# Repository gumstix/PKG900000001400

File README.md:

# Gumstix Raspberry Pi CM4 Development Board
## PKG900000001400 ![PKG900000001400][thumbnail]

Designed by Gumstix in Geppetto, the **Gumstix Raspberry Pi CM4 Development Board** brings the best of the CM4 to light, from PCIe to Gigabit Ethernet to dual CSI2 cameras.  Whether you're building a NAS server or a face-detecting robot, The CM4 Development board has built-in features that will help your project along.  It provides the following connections for breaking out the features of the Raspberry Pi CM4:

* Raspberry Pi 4 Header
* USB-UART Console Port
* DSI connector for connecting to displays
* 2 x CSI2 connector for connecting a camera
* HDMI port for audio/display
* Gigabit Ethernet port
* USB Type-A port for expandability
* M.2 (M Key) with single lane PCIe, compatible with 2280 NVMe drives and Google Coral

The CM4 Development board is ideal for various applications, Including:
* Network attached mass storage (NAS)
* Media Centers
* Edge AI
* Smart home management

__Links:__
* [AutoDoc Datasheet][autodoc]
* [Specifications][spec]
* [Store Page][store]
* [Schematics and Layout][hardware]

[thumbnail]: https://d3iwea566ns1n1.cloudfront.net/images/product/1ae94bd9fed173c4b6867992084763ec15bd388f.png
[autodoc]: PKG900000001400_AutoDoc.pdf
[spec]: PKG900000001400_SpecSheet.pdf
[store]: https://store.gumstix.com/cm4-development-board/
[hardware]: hardware/hardware.md
[firmware]: firmware/firmware.md

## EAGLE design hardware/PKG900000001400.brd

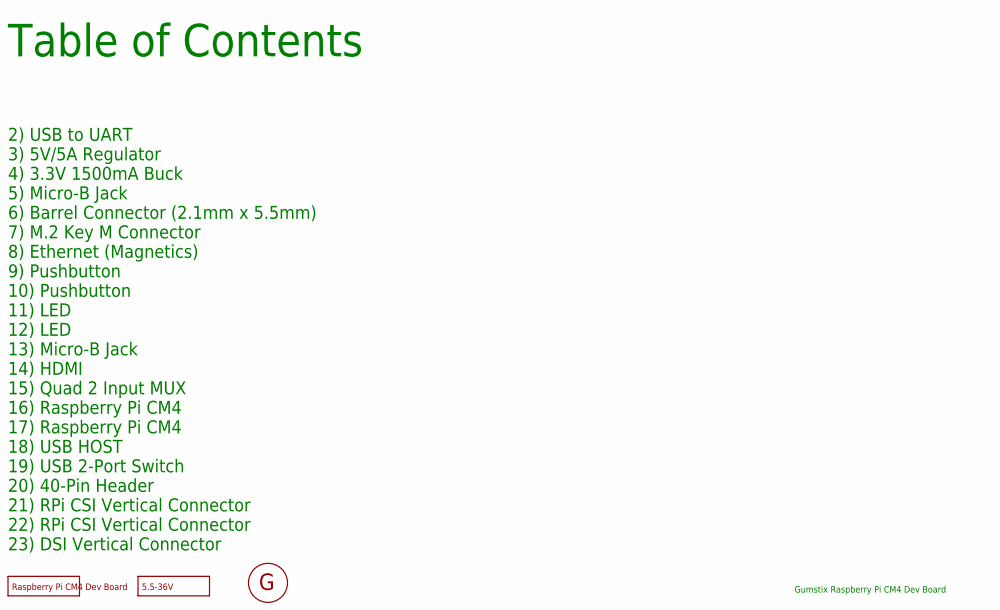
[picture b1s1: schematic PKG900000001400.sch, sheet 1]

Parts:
FD1, FD2, FD3, FD4, FD5, FD6, FD7, FD8: DNP; FIDUCIAL
U$3: DNP; GEPPETTO_LABEL
U$4: DNP; GEPPETTO_LOGO_SILK10
U$6: DNP; TIP_POSITIVE_LABEL; VOLTAGE 5.5-36V

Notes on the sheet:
Table of Contents
Gumstix Raspberry Pi CM4 Dev Board
2) USB to UART
3) 5V/5A Regulator
4) 3.3V 1500mA Buck
5) Micro-B Jack
6) Barrel Connector (2.1mm x 5.5mm)
7) M.2 Key M Connector
8) Ethernet (Magnetics)
9) Pushbutton
10) Pushbutton
11) LED
12) LED
13) Micro-B Jack
14) HDMI
15) Quad 2 Input MUX
16) Raspberry Pi CM4
17) Raspberry Pi CM4
18) USB HOST
19) USB 2-Port Switch
20) 40-Pin Header
21) RPi CSI Vertical Connector
22) RPi CSI Vertical Connector
23) DSI Vertical Connector

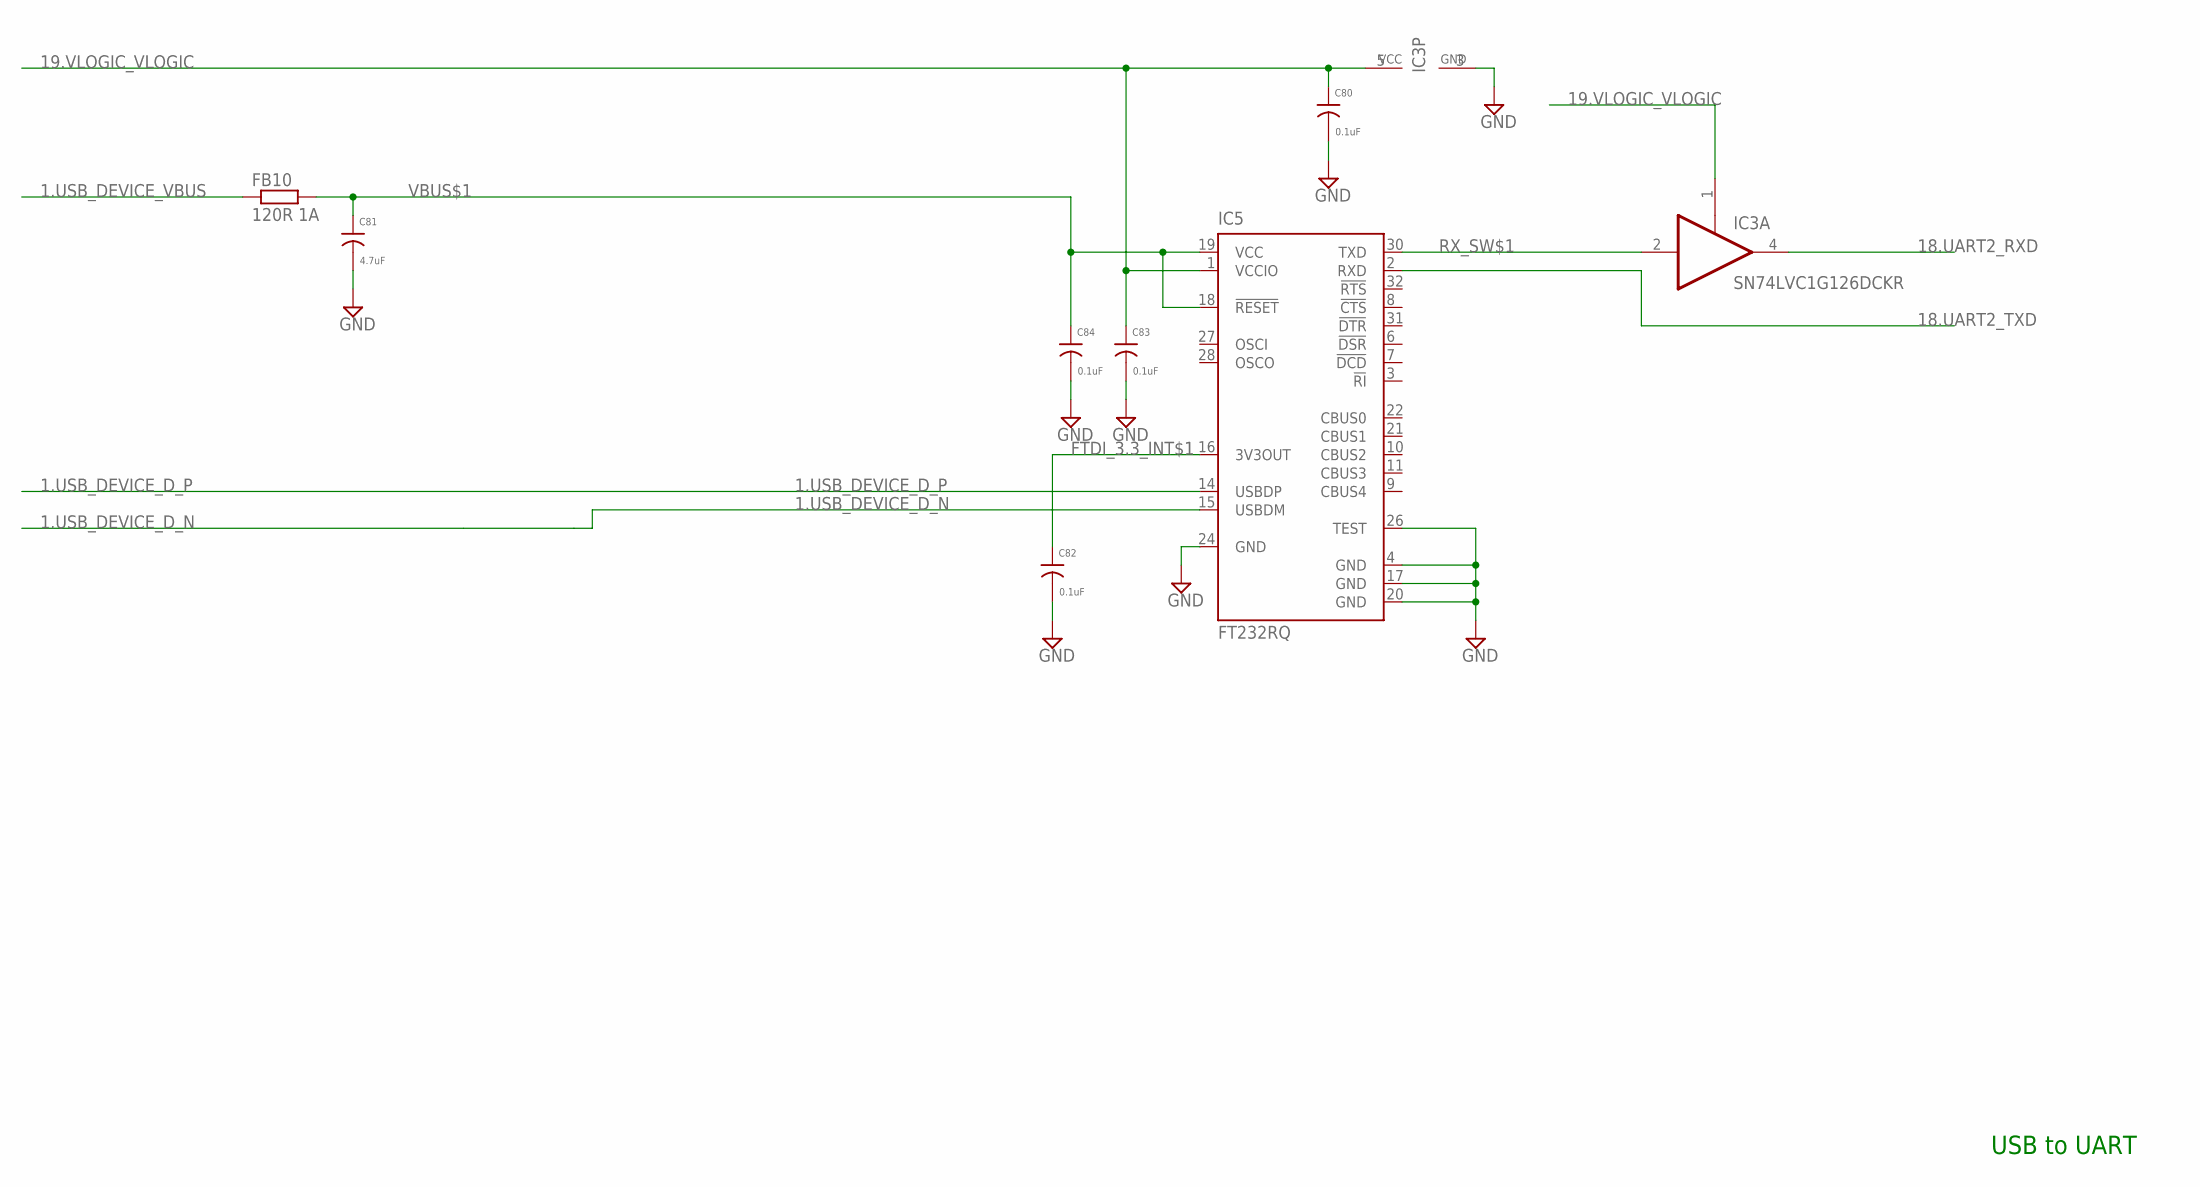
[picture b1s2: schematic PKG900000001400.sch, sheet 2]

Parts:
C80, C82, C83, C84: 0.1uF; 0201
C81: 4.7uF; 0603
FB10: 120R 1A; 0402
IC3: SN74LVC1G126DCKR; SC70-5
IC5: FT232RQ; QFN32

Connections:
1.USB_DEVICE_D_N: IC5.15 (USBDM); also elsewhere on the board
1.USB_DEVICE_D_P: IC5.14 (USBDP); also elsewhere on the board
1.USB_DEVICE_VBUS: FB10.1; also elsewhere on the board
18.UART2_RXD: IC3.4 (O); also elsewhere on the board
18.UART2_TXD: IC5.2 (RXD); also elsewhere on the board
19.VLOGIC_VLOGIC: C80.1, C83.1, IC3.1 (OE), IC3.5 (VCC), IC5.1 (VCCIO); also elsewhere on the board
FTDI_3.3_INT$1: C82.1, IC5.16 (3V3OUT)
GND: C80.2, C81.2, C82.2, C83.2, C84.2, IC3.3 (GND), IC5.4 (GND), IC5.17 (GND), IC5.20 (GND), IC5.24 (GND), IC5.26 (TEST); also elsewhere on the board
RX_SW$1: IC3.2 (I), IC5.30 (TXD)
VBUS$1: C81.1, C84.1, FB10.2, IC5.18 (!RESET), IC5.19 (VCC)

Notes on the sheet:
USB to UART

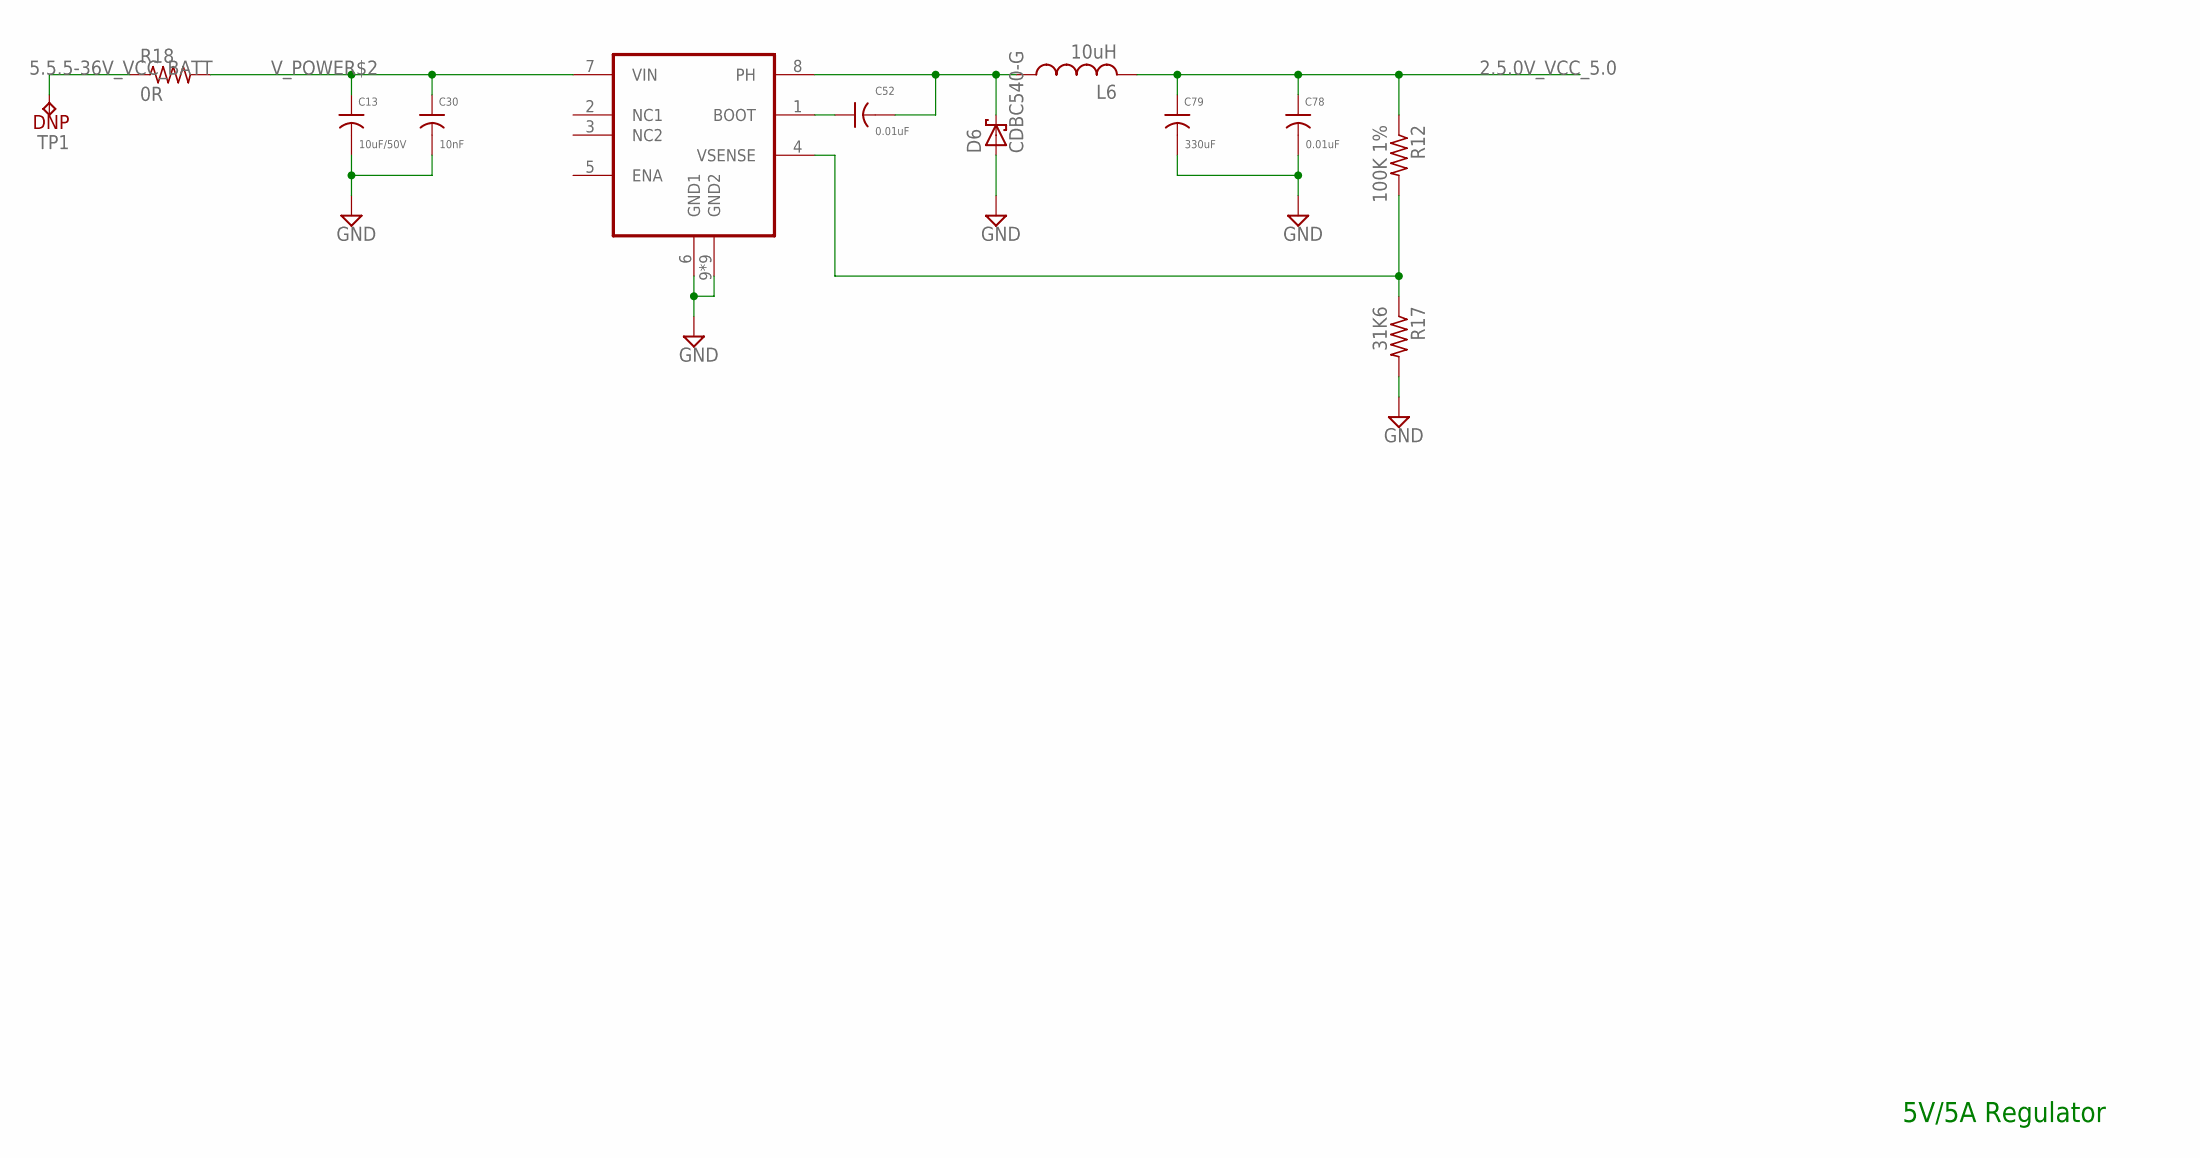
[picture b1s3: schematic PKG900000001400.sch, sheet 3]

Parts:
C13: 10uF/50V; 1206
C30: 10nF; 0603
C52, C78: 0.01uF; 0201
C79: 330uF; PANASONIC_F
D6: CDBC540-G; DO-214AB
L6: 10uH; 3232DZ
R12: 100K 1%; 0201
R17: 31K6; 0402
R18: 0R; 0805
TP1: DNP; TP0500
U7: TPS5450; 8SO_POWERPAD

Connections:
2.5.0V_VCC_5.0: C78.1, C79.+ (1), L6.2, R12.1; also elsewhere on the board
5.5.5-36V_VCC_BATT: R18.1, TP1.1; also elsewhere on the board
BOOT$2: C52.1, U7.1 (BOOT)
GND: C13.2, C30.2, C78.2, C79.- (2), D6.A, R17.2, U7.6 (GND1), U7.9 (GND2), U7.PWRPAD1 (GND2), U7.PWRPAD2 (GND2), U7.PWRPAD3 (GND2), U7.PWRPAD4 (GND2), U7.PWRPAD5 (GND2), U7.PWRPAD6 (GND2), U7.PWRPAD7 (GND2), U7.PWRPAD8 (GND2); also elsewhere on the board
PH$2: C52.2, D6.C, L6.1, U7.8 (PH)
VSENSE$2: R12.2, R17.1, U7.4 (VSENSE)
V_POWER$2: C13.1, C30.1, R18.2, U7.7 (VIN)

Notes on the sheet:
5V/5A Regulator

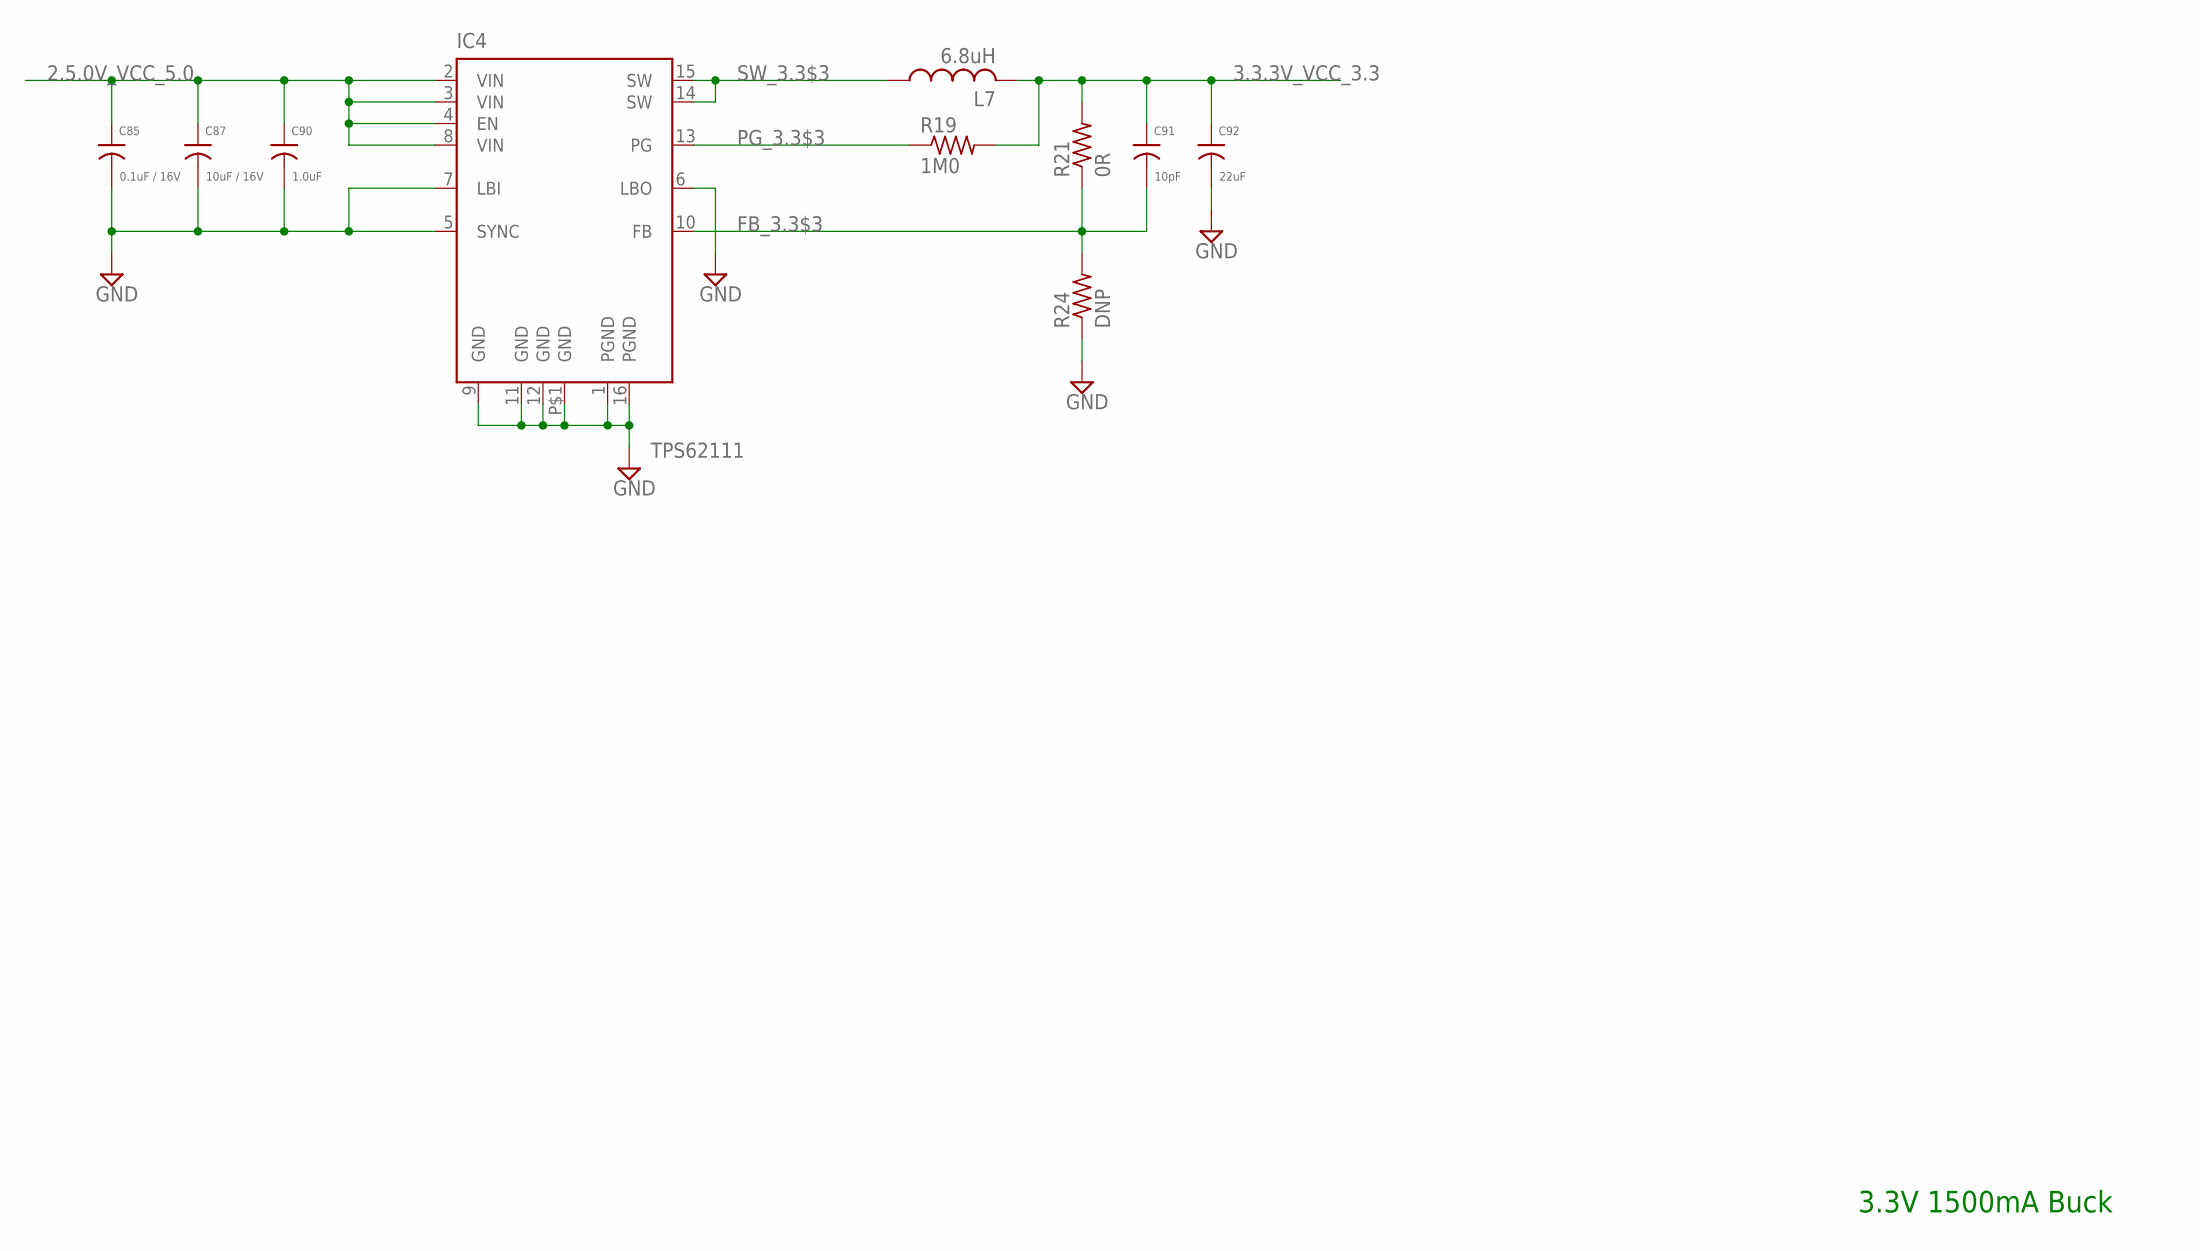
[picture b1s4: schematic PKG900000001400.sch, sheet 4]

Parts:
C85: 0.1uF / 16V; 0402
C87: 10uF / 16V; 0805
C90: 1.0uF; 0402
C91: 10pF; 0201
C92: 22uF; 0805
IC4: TPS62111; PQFP16
L7: 6.8uH; 1515
R19: 1M0; 0201
R21: 0R; 0402
R24: DNP; 0402

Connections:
2.5.0V_VCC_5.0: C85.1, C87.1, C90.1, IC4.2 (VIN), IC4.3 (VIN), IC4.4 (EN), IC4.8 (VIN); also elsewhere on the board
3.3.3V_VCC_3.3: C91.1, C92.1, L7.2, R19.2, R21.2; also elsewhere on the board
FB_3.3$3: C91.2, IC4.10 (FB), R21.1, R24.2
GND: C85.2, C87.2, C90.2, C92.2, IC4.1 (PGND), IC4.5 (SYNC), IC4.6 (LBO), IC4.7 (LBI), IC4.9 (GND), IC4.11 (GND), IC4.12 (GND), IC4.16 (PGND), IC4.P$1 (GND), R24.1; also elsewhere on the board
PG_3.3$3: IC4.13 (PG), R19.1
SW_3.3$3: IC4.14 (SW), IC4.15 (SW), L7.1

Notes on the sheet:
3.3V 1500mA Buck

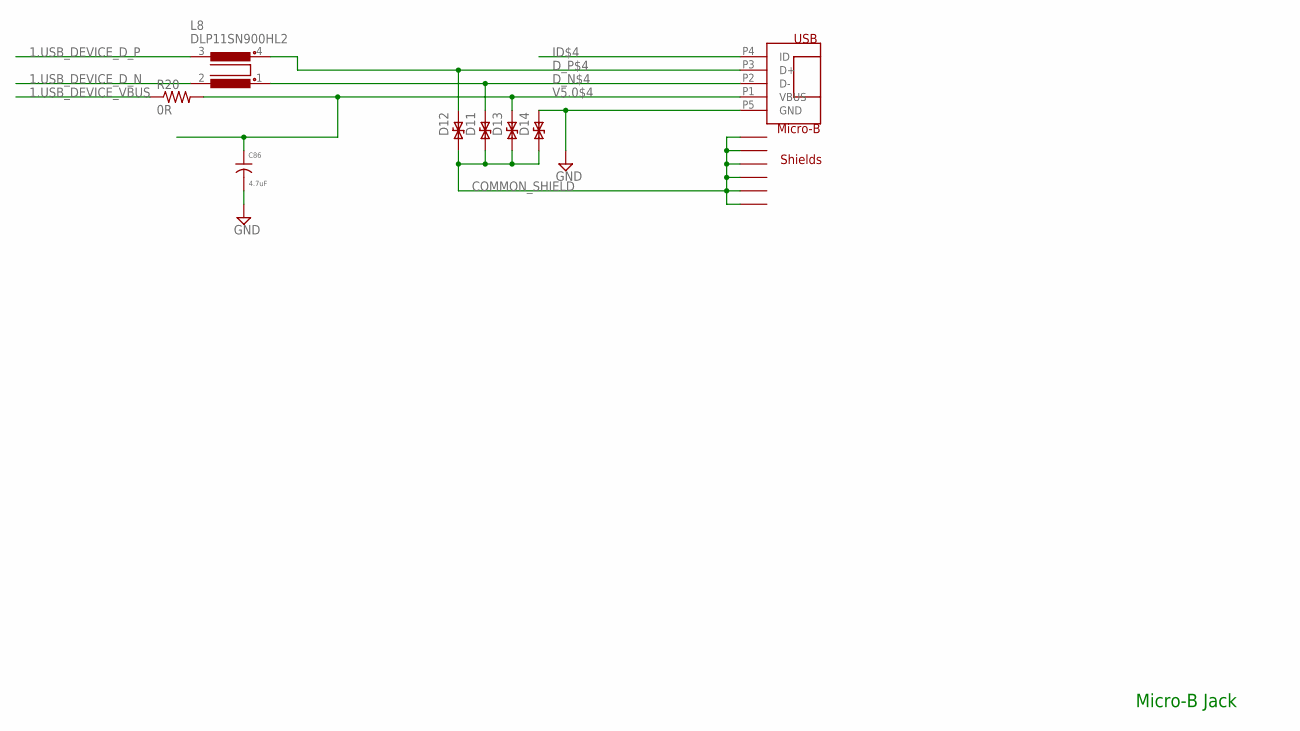
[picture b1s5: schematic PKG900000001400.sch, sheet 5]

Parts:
C86: 4.7uF; 0603
D11, D12: PS04LTVA1; D0402
D13, D14: B72590D50A060; D0402
J6: USB_MICRO_B
L8: DLP11SN900HL2; 0504-DLP11S
R20: 0R; 0201

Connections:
1.USB_DEVICE_D_N: L8.2; also elsewhere on the board
1.USB_DEVICE_D_P: L8.3; also elsewhere on the board
1.USB_DEVICE_VBUS: R20.1; also elsewhere on the board
COMMON_SHIELD: D11.P1, D12.P1, D13.P1, D14.P1, J6.COMMON_SHEILD1 (COMMON_SHIELD1), J6.COMMON_SHEILD2 (COMMON_SHIELD2), J6.COMMON_SHEILD3 (COMMON_SHIELD3), J6.COMMON_SHEILD4 (COMMON_SHIELD4), J6.COMMON_SHEILD5 (COMMON_SHIELD5), J6.COMMON_SHEILD6 (COMMON_SHIELD6); also elsewhere on the board
D_N$4: D11.P2, J6.P2 (D-), L8.1
D_P$4: D12.P2, J6.P3 (D+), L8.4
GND: C86.2, D14.P2, J6.P5 (GND); also elsewhere on the board
ID$4: J6.P4 (ID)
V5.0$4: C86.1, D13.P2, J6.P1 (VBUS), R20.2

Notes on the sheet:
Micro-B Jack

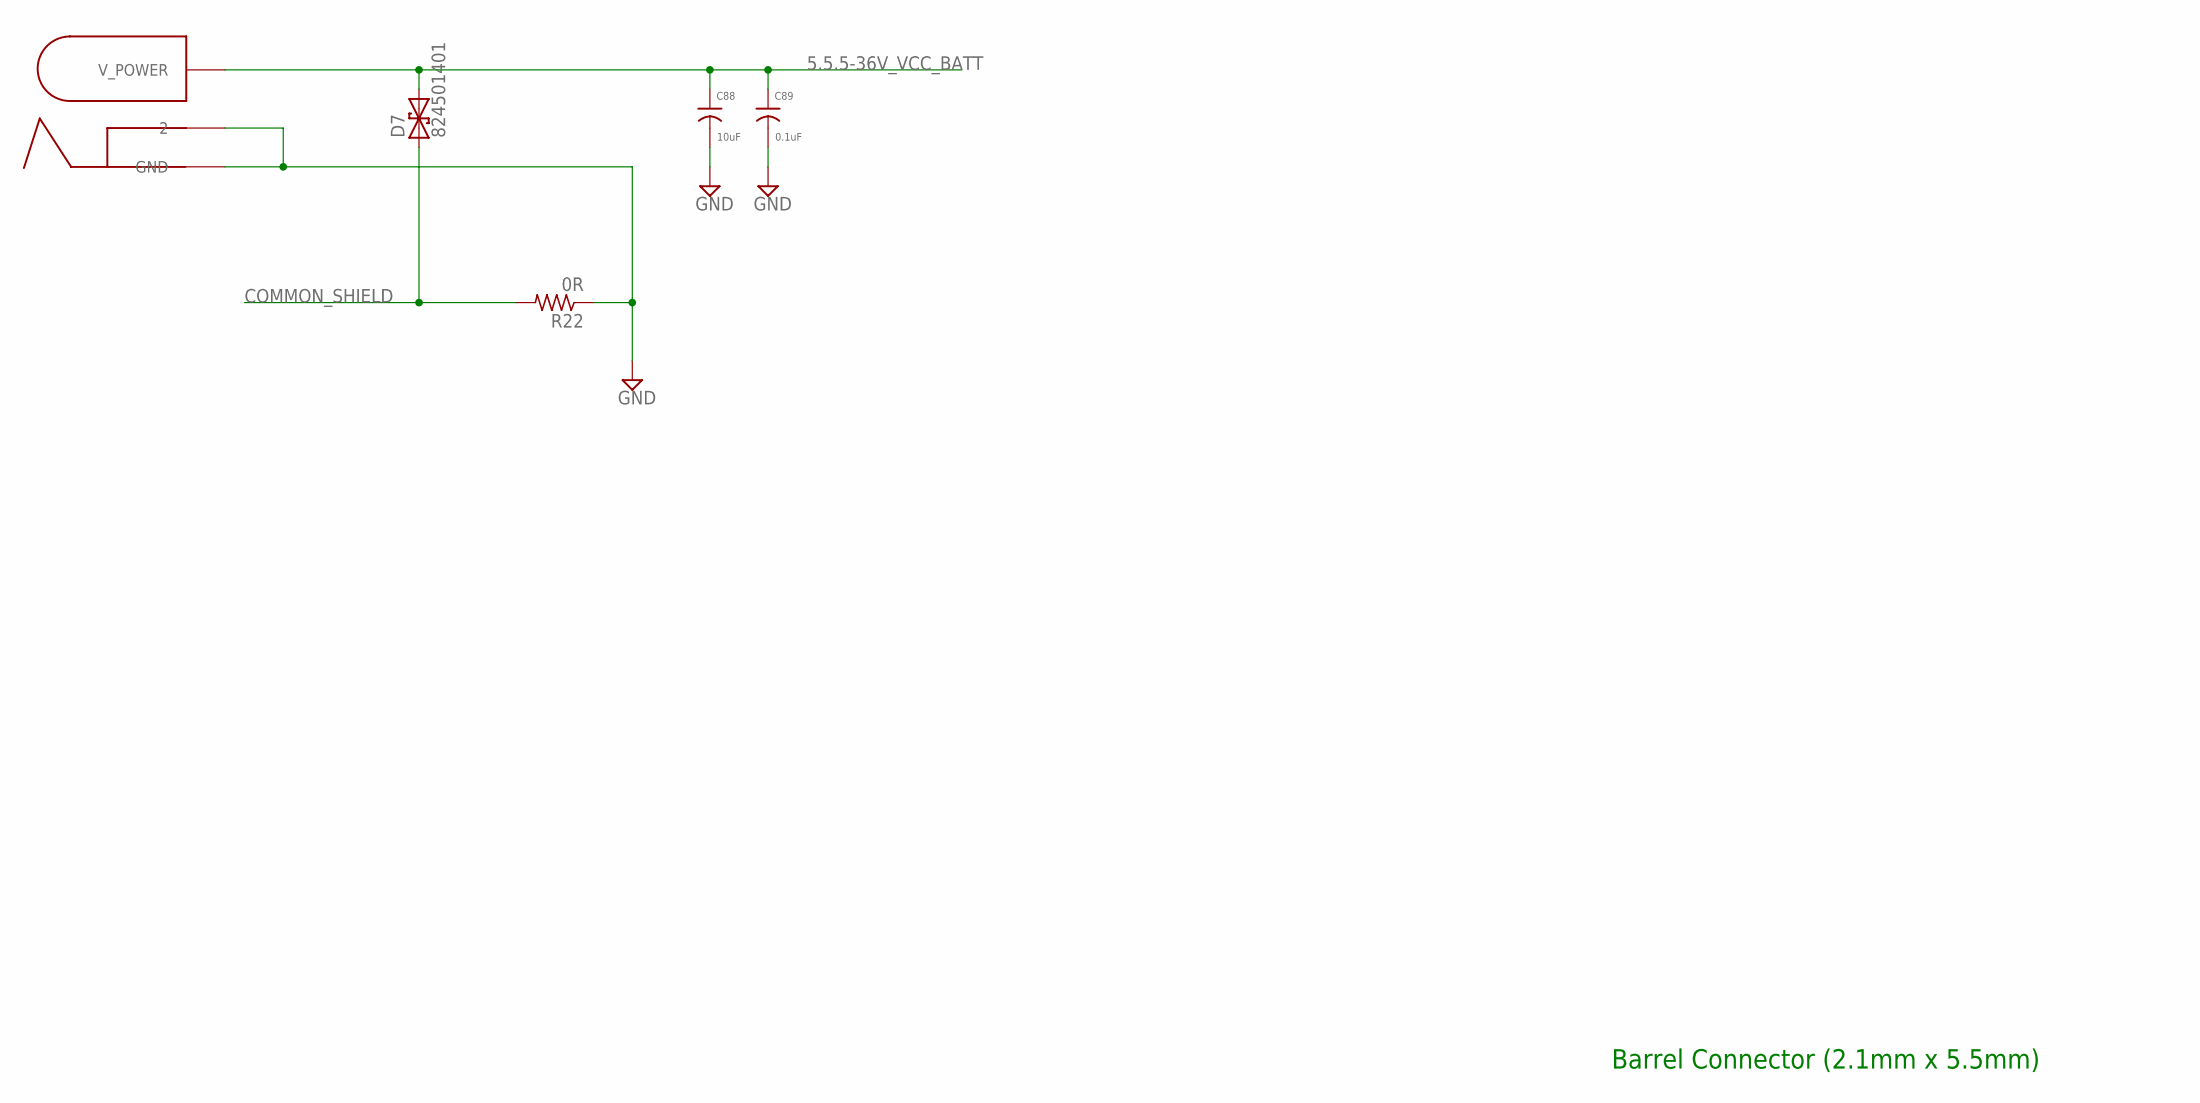
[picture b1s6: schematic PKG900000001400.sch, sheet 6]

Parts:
C88: 10uF; 0603
C89: 0.1uF; 0201
D7: 824501401; SMAJ
J3: PJ-002A
R22: 0R; 0201

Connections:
5.5.5-36V_VCC_BATT: C88.1, C89.1, D7.C (2), J3.1 (V_POWER); also elsewhere on the board
COMMON_SHIELD: D7.A (1), R22.2; also elsewhere on the board
GND: C88.2, C89.2, J3.2 (GND), J3.3 (2), R22.1; also elsewhere on the board

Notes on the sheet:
Barrel Connector (2.1mm x 5.5mm)

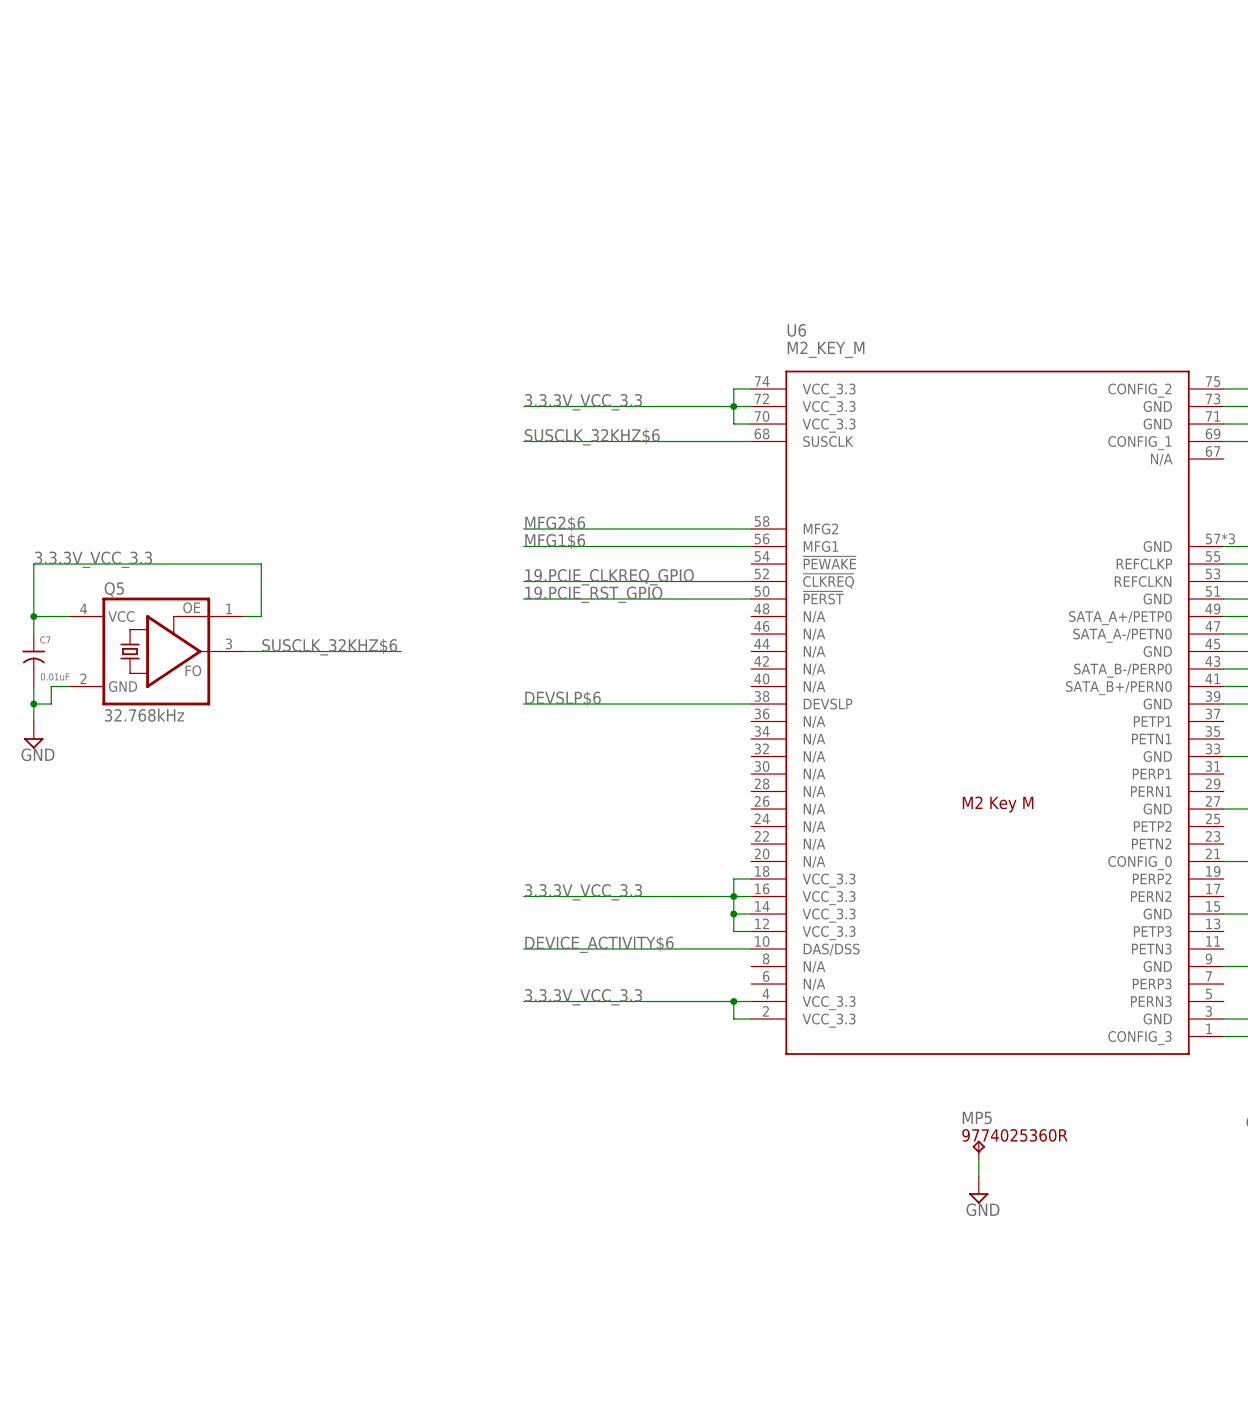
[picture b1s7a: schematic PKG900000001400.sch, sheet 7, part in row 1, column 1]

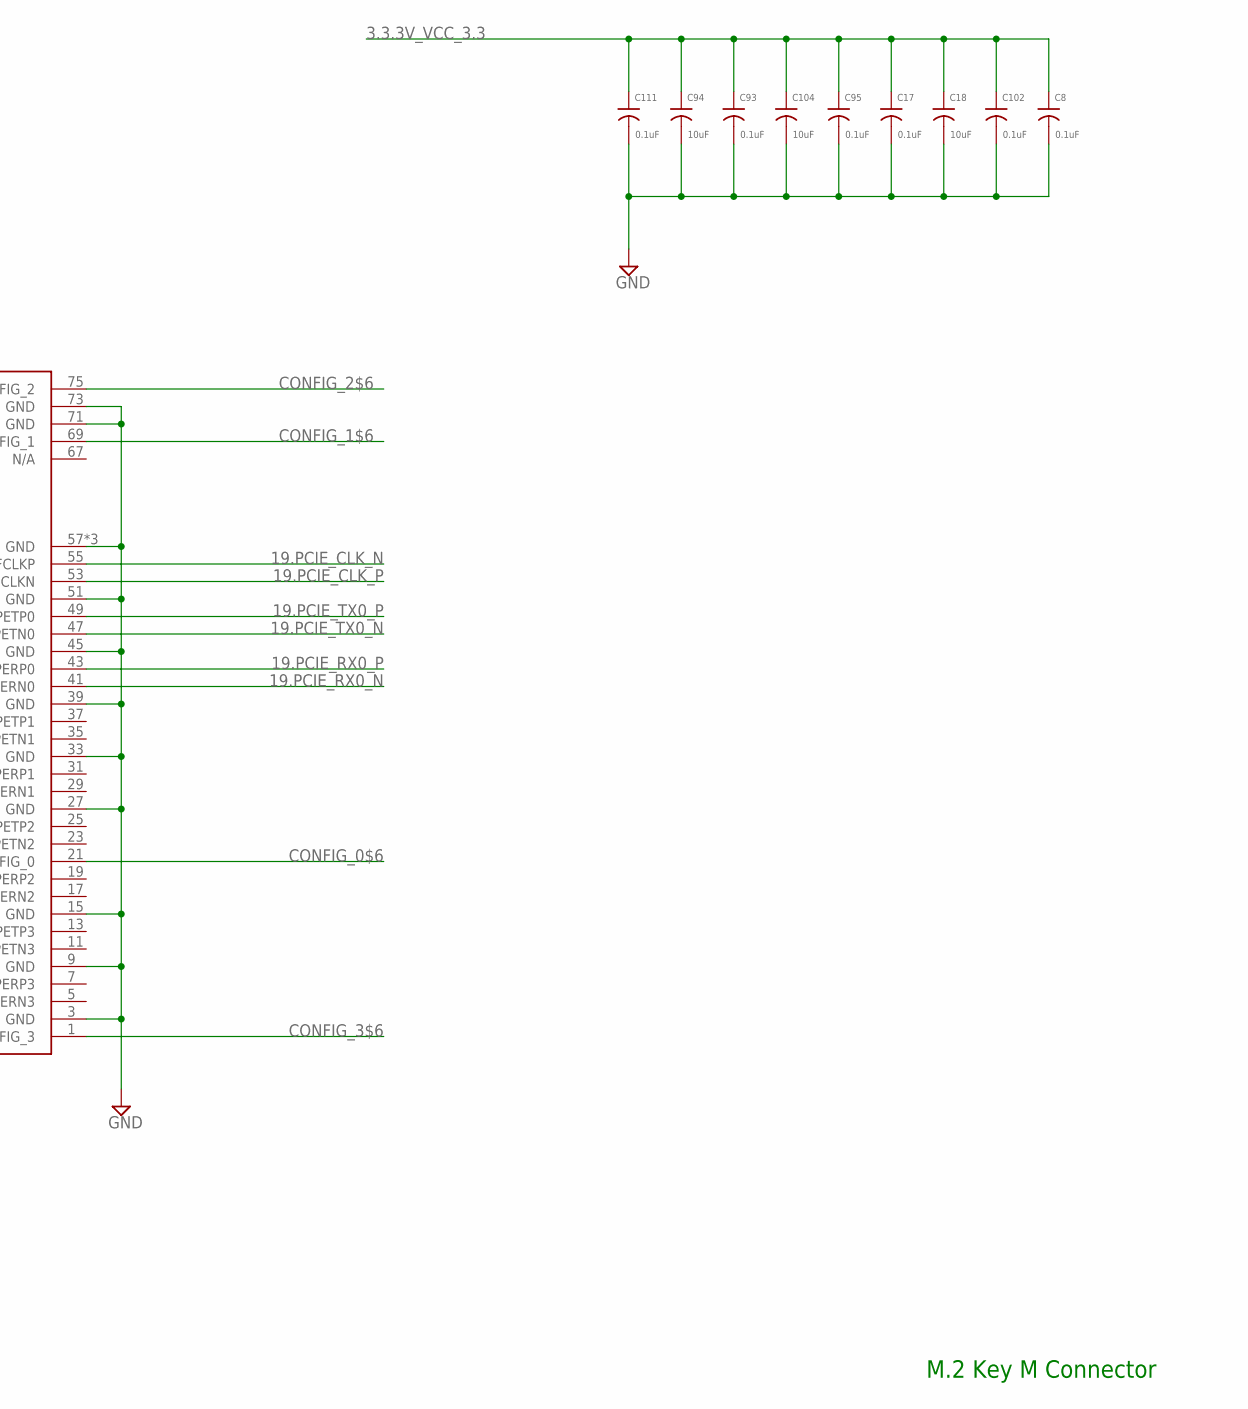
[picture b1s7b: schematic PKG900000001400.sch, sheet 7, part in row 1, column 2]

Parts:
C7: 0.01uF; 0201
C8, C17, C93, C95, C102, C111: 0.1uF; 0201
C18, C94, C104: 10uF; 0603
MP5: 9774025360R; WA-SMSI_9774___360
Q5: 32.768kHz; VLGA-4
U6: M2_KEY_M; 2199230_KEY_M

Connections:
3.3.3V_VCC_3.3: C7.1, C8.1, C17.1, C18.1, C93.1, C94.1, C95.1, C102.1, C104.1, C111.1, Q5.1 (OE), Q5.4 (VCC), U6.2 (VCC_3.3), U6.4 (VCC_3.3), U6.12 (VCC_3.3), U6.14 (VCC_3.3), U6.16 (VCC_3.3), U6.18 (VCC_3.3), U6.70 (VCC_3.3), U6.72 (VCC_3.3), U6.74 (VCC_3.3); also elsewhere on the board
19.PCIE_CLKREQ_GPIO: U6.52 (!CLKREQ); also elsewhere on the board
19.PCIE_CLK_N: U6.55 (REFCLKP); also elsewhere on the board
19.PCIE_CLK_P: U6.53 (REFCLKN); also elsewhere on the board
19.PCIE_RST_GPIO: U6.50 (!PERST); also elsewhere on the board
19.PCIE_RX0_N: U6.41 (SATA_B+/PERN0); also elsewhere on the board
19.PCIE_RX0_P: U6.43 (SATA_B-/PERP0); also elsewhere on the board
19.PCIE_TX0_N: U6.47 (SATA_A-/PETN0); also elsewhere on the board
19.PCIE_TX0_P: U6.49 (SATA_A+/PETP0); also elsewhere on the board
CONFIG_0$6: U6.21 (CONFIG_0)
CONFIG_1$6: U6.69 (CONFIG_1)
CONFIG_2$6: U6.75 (CONFIG_2)
CONFIG_3$6: U6.1 (CONFIG_3)
DEVICE_ACTIVITY$6: U6.10 (DAS/DSS)
DEVSLP$6: U6.38 (DEVSLP)
GND: C7.2, C8.2, C17.2, C18.2, C93.2, C94.2, C95.2, C102.2, C104.2, C111.2, MP5.1, Q5.2 (GND), U6.3 (GND), U6.9 (GND), U6.15 (GND), U6.27 (GND), U6.33 (GND), U6.39 (GND), U6.45 (GND), U6.51 (GND), U6.57 (GND), U6.71 (GND), U6.73 (GND), U6.P$1 (GND), U6.P$2 (GND); also elsewhere on the board
MFG1$6: U6.56 (MFG1)
MFG2$6: U6.58 (MFG2)
SUSCLK_32KHZ$6: Q5.3 (FO), U6.68 (SUSCLK)

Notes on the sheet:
M.2 Key M Connector

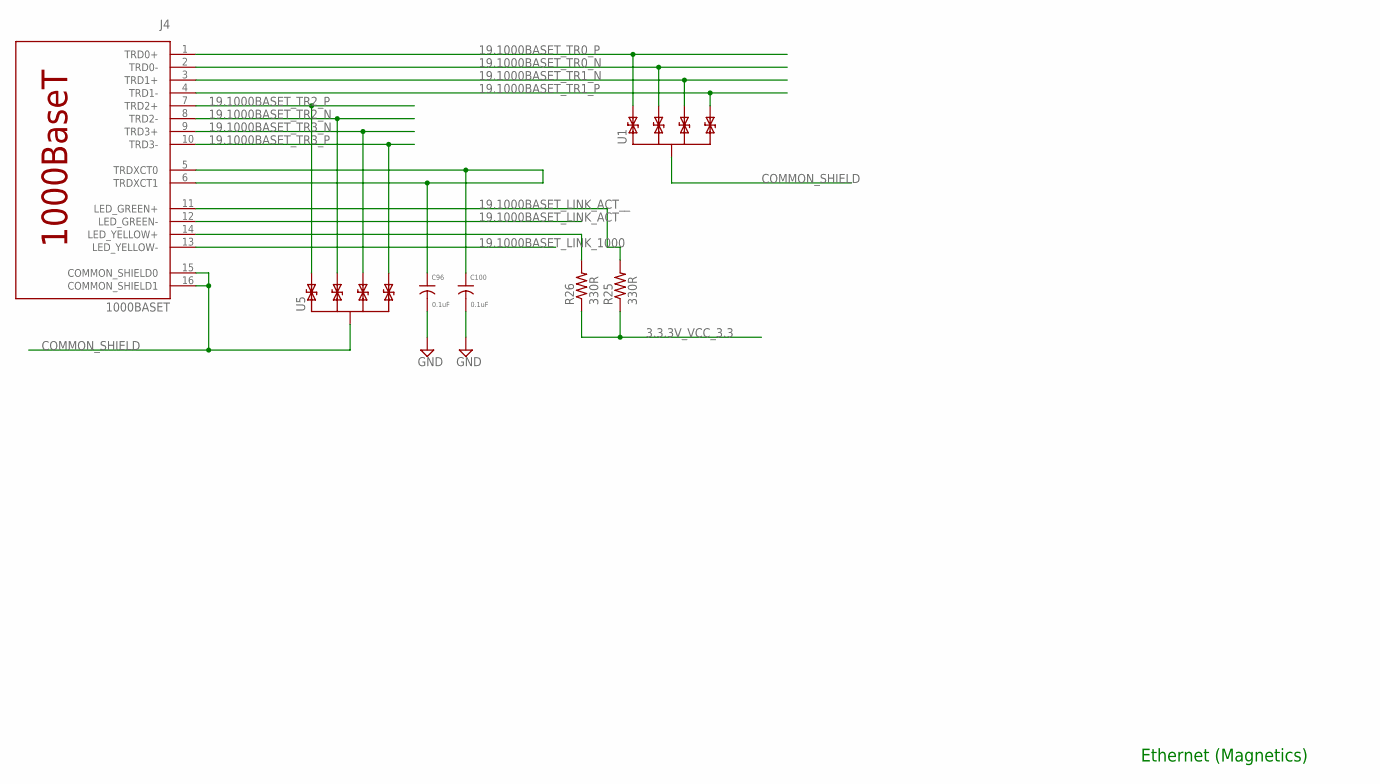
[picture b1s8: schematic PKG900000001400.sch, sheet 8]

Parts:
C96, C100: 0.1uF; 0201
J4: 1000BASET; 7499111447
R25, R26: 330R; 0201
U1, U5: TPD4E02B0410-USON; UFDFN-10

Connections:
3.3.3V_VCC_3.3: R25.1, R26.1; also elsewhere on the board
19.1000BASET_LINK_1000: J4.13 (LED_YELLOW-); also elsewhere on the board
19.1000BASET_LINK_ACT: J4.12 (LED_GREEN-); also elsewhere on the board
19.1000BASET_LINK_ACT__: J4.11 (LED_GREEN+), R25.2
19.1000BASET_TR0_N: J4.2 (TRD0-), U1.2, U1.9 (P2); also elsewhere on the board
19.1000BASET_TR0_P: J4.1 (TRD0+), U1.1, U1.10 (P1); also elsewhere on the board
19.1000BASET_TR1_N: J4.3 (TRD1+), U1.4 (P3), U1.7 (P3); also elsewhere on the board
19.1000BASET_TR1_P: J4.4 (TRD1-), U1.5 (P4), U1.6 (P4); also elsewhere on the board
19.1000BASET_TR2_N: J4.8 (TRD2-), U5.2, U5.9 (P2); also elsewhere on the board
19.1000BASET_TR2_P: J4.7 (TRD2+), U5.1, U5.10 (P1); also elsewhere on the board
19.1000BASET_TR3_N: J4.9 (TRD3+), U5.4 (P3), U5.7 (P3); also elsewhere on the board
19.1000BASET_TR3_P: J4.10 (TRD3-), U5.5 (P4), U5.6 (P4); also elsewhere on the board
COMMON_SHIELD: J4.15 (COMMON_SHIELD0), J4.16 (COMMON_SHIELD1), U1.3 (SHIELD), U1.8 (SHIELD), U5.3 (SHIELD), U5.8 (SHIELD); also elsewhere on the board
CT0$7: C96.1, C100.1, J4.5 (TRDXCT0), J4.6 (TRDXCT1)
GND: C96.2, C100.2; also elsewhere on the board
LED_YELLOW_P$7: J4.14 (LED_YELLOW+), R26.2

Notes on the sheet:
Ethernet (Magnetics)

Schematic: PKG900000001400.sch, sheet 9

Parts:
C97: 47pF; 0201
D8: B72590D50A060; D0402
R50: 10K 1%; 0201
R51: 150R; 0201
S2: EVQ

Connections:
19.NRESET_NRESET: C97.1, R51.2; also elsewhere on the board
19.VLOGIC_VLOGIC: R50.2; also elsewhere on the board
BTN_A$12: D8.P2, R50.1, R51.1, S2.B@2 (B')
GND: C97.2, D8.P1, S2.A@1 (A); also elsewhere on the board

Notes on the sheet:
Pushbutton

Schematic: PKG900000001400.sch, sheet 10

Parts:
C98: 47pF; 0201
D9: B72590D50A060; D0402
R30: 10K 1%; 0201
R31: 150R; 0201
S3: EVQ

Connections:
19.GPIO24_GPIO: C98.1, R31.2; also elsewhere on the board
19.VLOGIC_VLOGIC: R30.2; also elsewhere on the board
BTN_A$13: D9.P2, R30.1, R31.1, S3.B@2 (B')
GND: C98.2, D9.P1, S3.A@1 (A); also elsewhere on the board

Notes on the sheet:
Pushbutton

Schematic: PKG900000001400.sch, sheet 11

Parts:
D10: RED; D0603
Q6: BSS138; SOT23
R32: 1K; 0201
R33: 300R; 0402
R34: 100K 1%; 0201

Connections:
3.3.3V_VCC_3.3: R33.2; also elsewhere on the board
19.GPIO23_GPIO: R32.1, R34.2; also elsewhere on the board
ANODE$14: D10.A, R33.1
GATE$14: Q6.1 (G), R32.2
GND: Q6.2 (S), R34.1; also elsewhere on the board
LED-$14: D10.C, Q6.3 (D)

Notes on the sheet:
LED

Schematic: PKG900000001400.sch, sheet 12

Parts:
D15: GREEN; D0603
Q4: BSS138; SOT23
R35: 300R; 0402
R36: 100K 1%; 0201
R46: 1K; 0201

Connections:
3.3.3V_VCC_3.3: R35.2; also elsewhere on the board
19.SYS_EN_SYSEN: R36.2, R46.1; also elsewhere on the board
ANODE$15: D15.A, R35.1
GATE$15: Q4.1 (G), R46.2
GND: Q4.2 (S), R36.1; also elsewhere on the board
LED-$15: D15.C, Q4.3 (D)

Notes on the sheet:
LED

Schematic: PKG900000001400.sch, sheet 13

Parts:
C99: 4.7uF; 0603
D5, D18: B72590D50A060; D0402
D16, D17: PS04LTVA1; D0402
J5: USB_MICRO_B
L5: DLP11SN900HL2; 0504-DLP11S
R37: 0R; 0201

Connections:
21.USB2_D_N: L5.2; also elsewhere on the board
21.USB2_D_P: L5.3; also elsewhere on the board
21.USB2_VBUS: R37.1; also elsewhere on the board
COMMON_SHIELD: D5.P1, D16.P1, D17.P1, D18.P1, J5.COMMON_SHEILD1 (COMMON_SHIELD1), J5.COMMON_SHEILD2 (COMMON_SHIELD2), J5.COMMON_SHEILD3 (COMMON_SHIELD3), J5.COMMON_SHEILD4 (COMMON_SHIELD4), J5.COMMON_SHEILD5 (COMMON_SHIELD5), J5.COMMON_SHEILD6 (COMMON_SHIELD6); also elsewhere on the board
D_N$16: D17.P2, J5.P2 (D-), L5.1
D_P$16: D16.P2, J5.P3 (D+), L5.4
GND: C99.2, D5.P2, J5.P5 (GND); also elsewhere on the board
ID$16: J5.P4 (ID)
V5.0$16: C99.1, D18.P2, J5.P1 (VBUS), R37.2

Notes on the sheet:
Micro-B Jack

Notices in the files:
parts and their libraries:
qualified_1: COMPANY_AND_YEAR: Geppetto, Gumstix Inc (c) 2019
